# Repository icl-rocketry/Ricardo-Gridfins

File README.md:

# Ricardo-Gridfins
gridfin controller

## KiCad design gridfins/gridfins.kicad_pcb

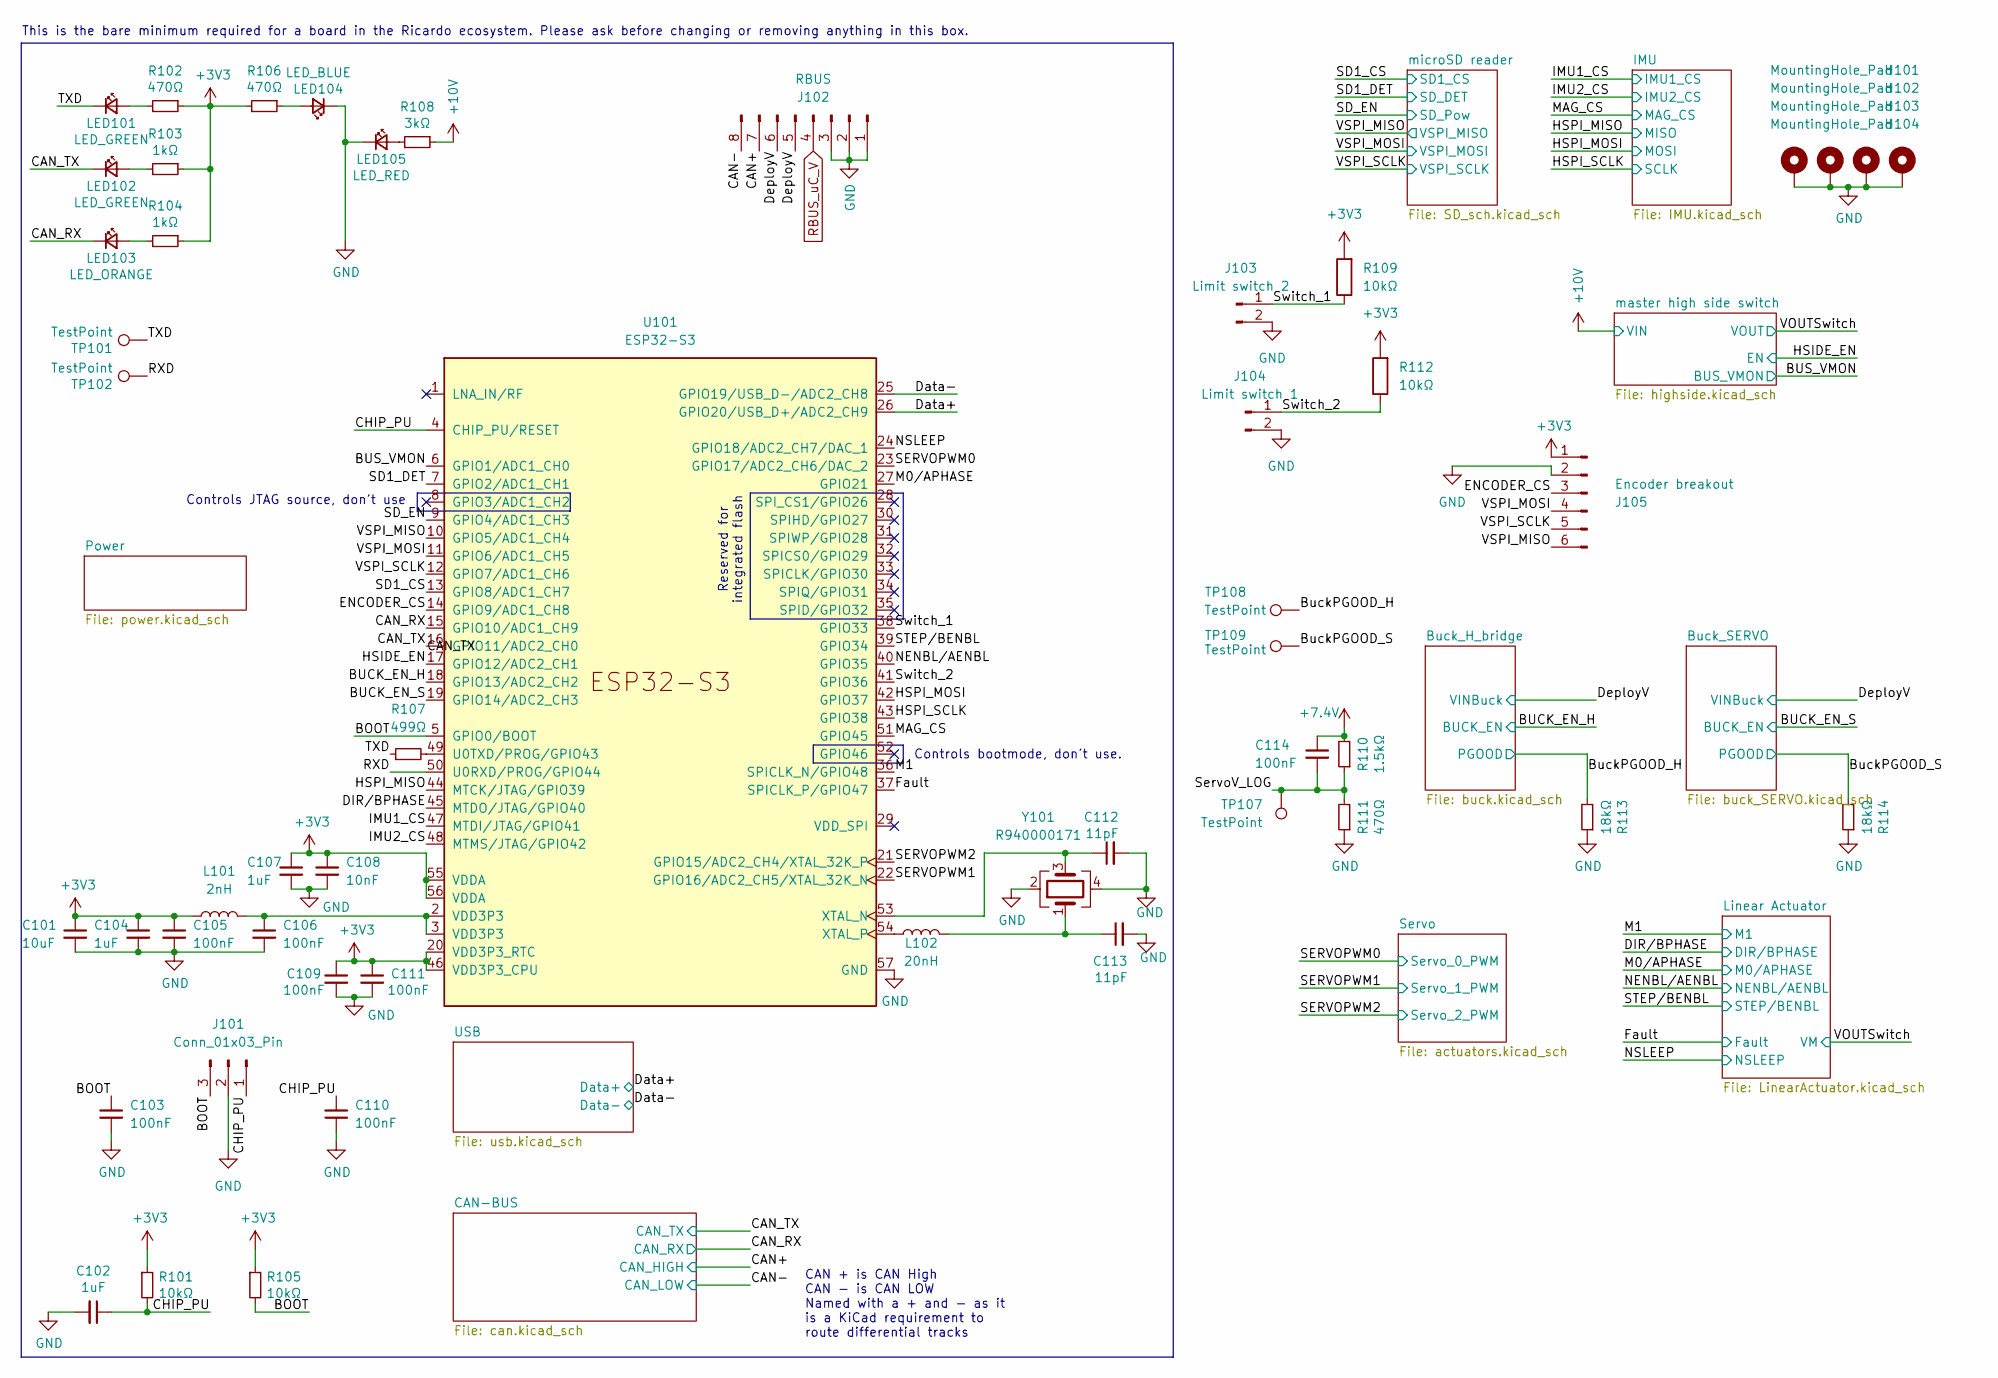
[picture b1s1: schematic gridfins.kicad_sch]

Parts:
C101: 10uF; C_0402_1005Metric
C102, C104, C107: 1uF; C_0402_1005Metric
C103, C105, C106, C109, C110, C111, C114: 100nF; C_0402_1005Metric
C108: 10nF; C_0402_1005Metric
C112, C113: 11pF; C_0402_1005Metric
H101, H102, H103, H104: MountingHole_Pad; MountingHole_3.2mm_M3_DIN965_Pad
J101: Conn_01x03_Pin; PinHeader_1x03_P1.00mm_Vertical
J102: RBUS; Molex_Mini-Fit_Jr_5569-08A2_2x04_P4.20mm_Horizontal
J103: Limit switch 2; PinHeader_1x02_P2.54mm_Vertical
J104: Limit switch 1; PinHeader_1x02_P2.54mm_Vertical
J105: Encoder breakout; PinHeader_2x03_P2.54mm_Vertical
L101: 2nH; L_0402_1005Metric
L102: 20nH; L_0402_1005Metric
LED101, LED102: LED_GREEN; LED_0402_1005Metric
LED103: LED_ORANGE; LED_0402_1005Metric
LED104: LED_BLUE; LED_0402_1005Metric
LED105: LED_RED; LED_0402_1005Metric
R101, R105, R109, R112: 10kΩ; R_0402_1005Metric
R102, R106, R111: 470Ω; R_0402_1005Metric
R103, R104: 1kΩ; R_0402_1005Metric
R107: 499Ω; R_0402_1005Metric
R108: 3kΩ; R_0402_1005Metric
R110: 1.5kΩ; R_0402_1005Metric
R113, R114: 18kΩ; R_0402_1005Metric
TP101, TP102, TP107, TP108, TP109: TestPoint; TestPoint_Pad_D1.0mm
U101: ESP32-S3; QFN40P700X700X90-57N
Y101: R940000171; Crystal_SMD_2016-4Pin_2.0x1.6mm

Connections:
+3V3: C101.1, C104.1, C105.1, C107.1, C108.1, C109.1, C111.1, J105.1, L101.1, R101.1, R102.1, R103.1, R104.1, R105.1, R106.2, R109.2, R112.2, U101.20 (VDD3P3_RTC), U101.46 (VDD3P3_CPU), U101.55 (VDDA), U101.56 (VDDA); also elsewhere on the board
+7.4V: C114.1, R110.2; also elsewhere on the board
+10V: R108.1; also elsewhere on the board
/BOOT: C103.1, J101.3, R105.2, U101.5 (GPIO0/BOOT)
/BUCK_EN_H: U101.18 (GPIO13/ADC2_CH2); also elsewhere on the board
/BUCK_EN_S: U101.19 (GPIO14/ADC2_CH3); also elsewhere on the board
/BUS_VMON: U101.6 (GPIO1/ADC1_CH0); also elsewhere on the board
/BuckPGOOD_H: R113.2, TP108.1 (1_1); also elsewhere on the board
/BuckPGOOD_S: R114.2, TP109.1 (1_1); also elsewhere on the board
/CAN+: J102.7; also elsewhere on the board
/CAN-: J102.8; also elsewhere on the board
/CAN_RX: LED103.1 (K), U101.15 (GPIO10/ADC1_CH9); also elsewhere on the board
/CAN_TX: LED102.1 (K), U101.16 (GPIO11/ADC2_CH0); also elsewhere on the board
/CHIP_PU: C102.1, C110.2, J101.1, R101.2, U101.4 (CHIP_PU/RESET)
/DIR/BPHASE: U101.45 (MTDO/JTAG/GPIO40); also elsewhere on the board
/Data+: U101.26 (GPIO20/USB_D+/ADC2_CH9); also elsewhere on the board
/Data-: U101.25 (GPIO19/USB_D-/ADC2_CH8); also elsewhere on the board
/DeployV: J102.5, J102.6; also elsewhere on the board
/ENCODER_CS: J105.3, U101.14 (GPIO9/ADC1_CH8)
/Fault: U101.37 (SPICLK_P/GPIO47); also elsewhere on the board
/HSIDE_EN: U101.17 (GPIO12/ADC2_CH1); also elsewhere on the board
/HSPI_MISO: U101.44 (MTCK/JTAG/GPIO39); also elsewhere on the board
/HSPI_MOSI: U101.42 (GPIO37); also elsewhere on the board
/HSPI_SCLK: U101.43 (GPIO38); also elsewhere on the board
/IMU1_CS: U101.47 (MTDI/JTAG/GPIO41); also elsewhere on the board
/IMU2_CS: U101.48 (MTMS/JTAG/GPIO42); also elsewhere on the board
/M0/APHASE: U101.27 (GPIO21); also elsewhere on the board
/M1: U101.36 (SPICLK_N/GPIO48); also elsewhere on the board
/MAG_CS: U101.51 (GPIO45); also elsewhere on the board
/NENBL/AENBL: U101.40 (GPIO35); also elsewhere on the board
/NSLEEP: U101.24 (GPIO18/ADC2_CH7/DAC_1); also elsewhere on the board
/RXD: TP102.1 (1_1), U101.50 (U0RXD/PROG/GPIO44)
/SD1_CS: U101.13 (GPIO8/ADC1_CH7); also elsewhere on the board
/SD1_DET: U101.7 (GPIO2/ADC1_CH1); also elsewhere on the board
/SD_EN: U101.9 (GPIO4/ADC1_CH3); also elsewhere on the board
/SERVOPWM0: U101.23 (GPIO17/ADC2_CH6/DAC_2); also elsewhere on the board
/SERVOPWM1: U101.22 (GPIO16/ADC2_CH5/XTAL_32K_N); also elsewhere on the board
/SERVOPWM2: U101.21 (GPIO15/ADC2_CH4/XTAL_32K_P); also elsewhere on the board
/STEP/BENBL: U101.39 (GPIO34); also elsewhere on the board
/ServoV_LOG: C114.2, R110.1, R111.2, TP107.1 (1_1)
/Switch_1: J103.1, R109.1, U101.38 (GPIO33)
/Switch_2: J104.1, R112.1, U101.41 (GPIO36)
/TXD: LED101.1 (K), R107.1, TP101.1 (1_1)
/VSPI_MISO: J105.6, U101.10 (GPIO5/ADC1_CH4); also elsewhere on the board
/VSPI_MOSI: J105.4, U101.11 (GPIO6/ADC1_CH5); also elsewhere on the board
/VSPI_SCLK: J105.5, U101.12 (GPIO7/ADC1_CH6); also elsewhere on the board
GND: C101.2, C102.2, C103.2, C104.2, C105.2, C106.2, C107.2, C108.2, C109.2, C110.1, C111.2, C112.2, C113.2, H101.1 (1_1), H102.1 (1_1), H103.1 (1_1), H104.1 (1_1), J101.2, J102.1, J102.2, J102.3, J103.2, J104.2, J105.2, LED104.1 (K), LED105.1 (K), R111.1, R113.1, R114.1, U101.57 (GND), Y101.2, Y101.4; also elsewhere on the board
unnamed: C106.1, L101.2, U101.2 (VDD3P3), U101.3 (VDD3P3)
unnamed: C113.1, L102.2, Y101.1
unnamed: LED101.2 (A), R102.2
unnamed: LED102.2 (A), R103.2
unnamed: LED103.2 (A), R104.2
unnamed: LED104.2 (A), R106.1
unnamed: LED105.2 (A), R108.2
unnamed: R107.2, U101.49 (U0TXD/PROG/GPIO43)
unnamed: C112.1, U101.53 (XTAL_N), Y101.3
unnamed: L102.1, U101.54 (XTAL_P)
RBUS_uC_V: J102.4; also elsewhere on the board

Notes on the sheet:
Controls bootmode, don't use.
This is the bare minimum required for a board in the Ricardo ecosystem. Please ask before changing or removing anything in this box.
CAN + is CAN High CAN - is CAN LOW Named with a + and - as it is a KiCad requirement to route differential tracks
Controls JTAG source, don't use
Reserved for integrated flash

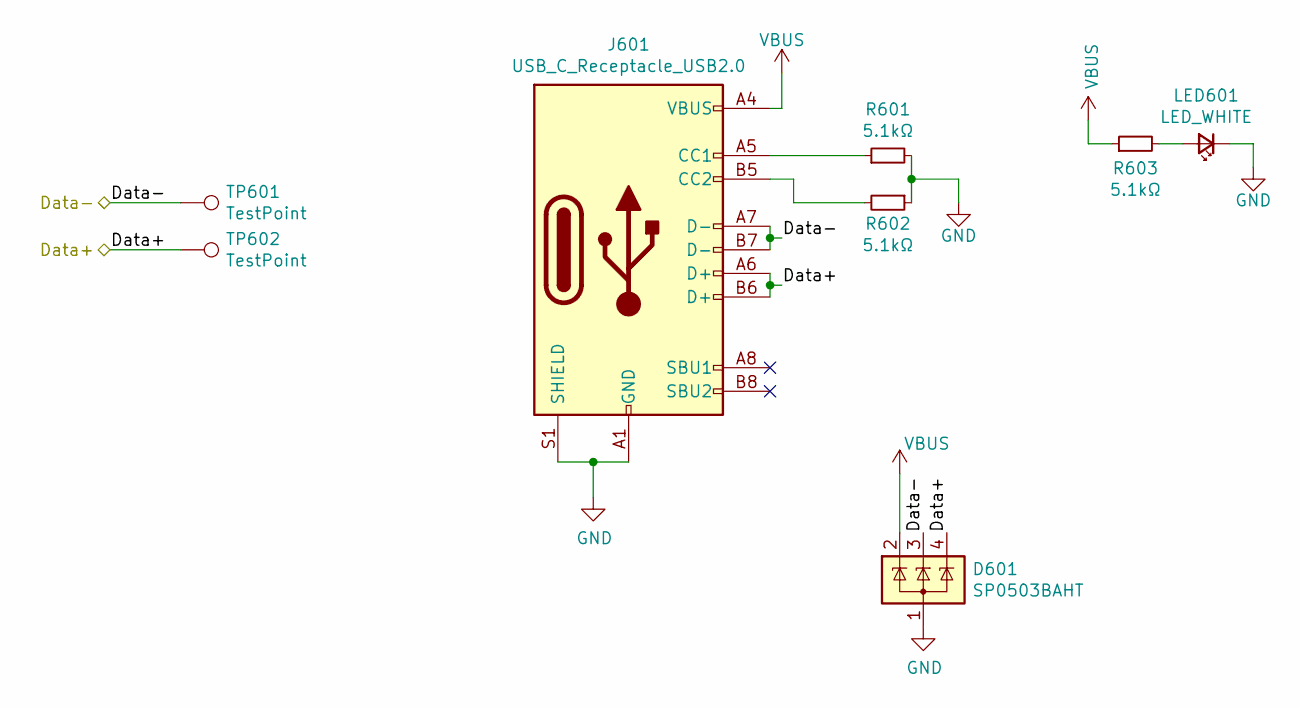
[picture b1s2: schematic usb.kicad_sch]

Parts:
D601: SP0503BAHT; SOT-143
J601: USB_C_Receptacle_USB2.0; USB_C_Receptacle_Palconn_UTC16-G
LED601: LED_WHITE; LED_0402_1005Metric
R601, R602, R603: 5.1kΩ; R_0402_1005Metric
TP601, TP602: TestPoint; TestPoint_Pad_D1.0mm

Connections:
/Data+: D601.4 (K), J601.A6 (D+), J601.B6 (D+), TP602.1 (1_1); also elsewhere on the board
/Data-: D601.3 (K), J601.A7 (D-), J601.B7 (D-), TP601.1 (1_1); also elsewhere on the board
GND: D601.1 (A), J601.A1 (GND), J601.A12 (GND), J601.B1 (GND), J601.B12 (GND), J601.S1 (SHIELD), LED601.1 (K), R601.2, R602.1; also elsewhere on the board
unnamed: J601.A5 (CC1), R601.1
unnamed: J601.B5 (CC2), R602.2
unnamed: LED601.2 (A), R603.2
VBUS: D601.2 (K), J601.A4 (VBUS), J601.A9 (VBUS), J601.B4 (VBUS), J601.B9 (VBUS), R603.1; also elsewhere on the board

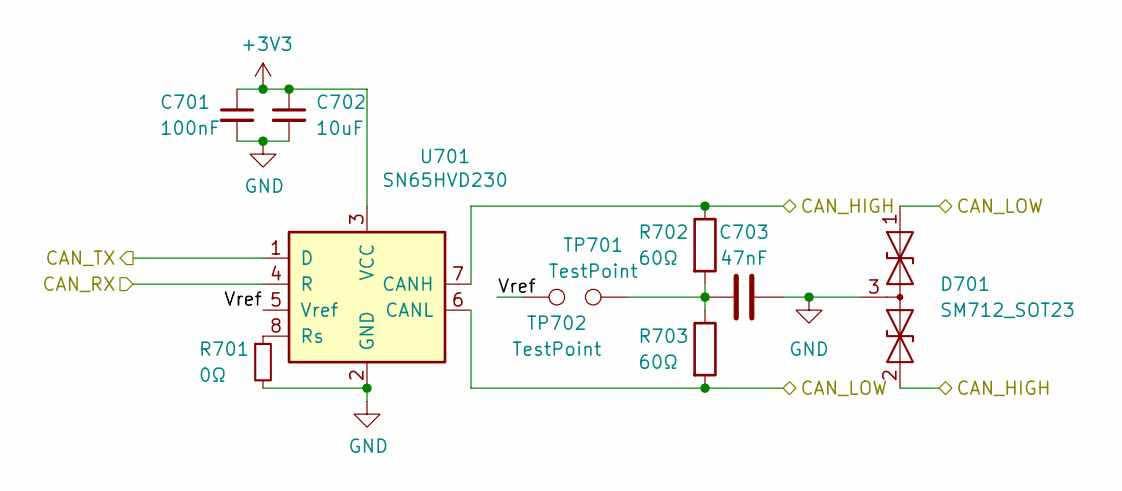
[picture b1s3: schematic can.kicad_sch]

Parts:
C701: 100nF; C_0402_1005Metric
C702: 10uF; C_0402_1005Metric
C703: 47nF; C_0402_1005Metric
D701: SM712_SOT23; SOT-23
R701: 0Ω; R_0603_1608Metric
R702, R703: 60Ω; R_0603_1608Metric
TP701, TP702: TestPoint
U701: SN65HVD230; SOIC-8_3.9x4.9mm_P1.27mm

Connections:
+3V3: C701.1, C702.1, U701.3 (VCC); also elsewhere on the board
/CAN+: D701.2 (A2), R702.1, U701.7 (CANH); also elsewhere on the board
/CAN-: D701.1 (A1), R703.2, U701.6 (CANL); also elsewhere on the board
/CAN-BUS/Vref: TP702.1 (1_1), U701.5 (Vref)
/CAN_RX: U701.4 (R); also elsewhere on the board
/CAN_TX: U701.1 (D); also elsewhere on the board
GND: C701.2, C702.2, C703.2, D701.3 (common), R701.2, U701.2 (GND); also elsewhere on the board
unnamed: C703.1, R702.2, R703.1, TP701.1 (1_1)
unnamed: R701.1, U701.8 (Rs)

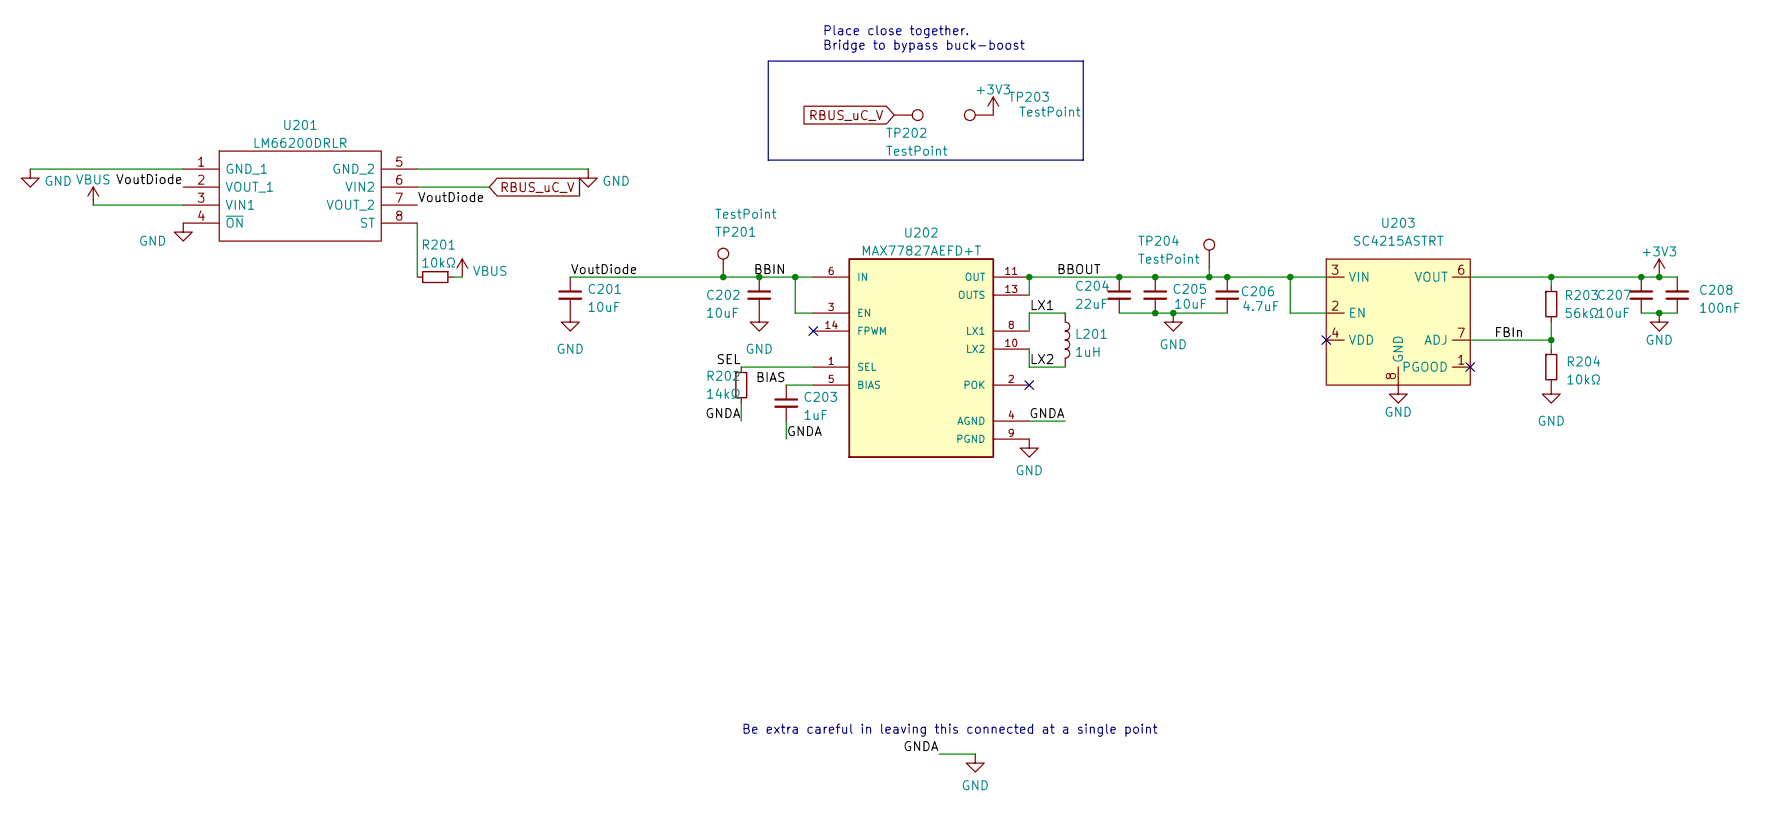
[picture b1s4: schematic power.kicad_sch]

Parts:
C201, C205, C207: 10uF; C_0402_1005Metric
C202: 10uF; C_0603_1608Metric
C203: 1uF; C_0402_1005Metric
C204: 22uF; C_0603_1608Metric
C206: 4.7uF; C_0402_1005Metric
C208: 100nF; C_0402_1005Metric
L201: 1uH; L_0805_2012Metric
R201, R204: 10kΩ; R_0402_1005Metric
R202: 14kΩ; R_0402_1005Metric
R203: 56kΩ; R_0402_1005Metric
TP201, TP202, TP203, TP204: TestPoint; TestPoint_Pad_D1.5mm
U201: LM66200DRLR; SOTFL50P160X60-8N; Manufacturer_Part_Number LM66200DRLR; Mouser Part Number 595-LM66200DRLR
U202: MAX77827AEFD+T; CONV_MAX77827AEFD+T; PARTREV B
U203: SC4215ASTRT; SOIC127P599X175-9N

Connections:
+3V3: C207.2, C208.2, R203.1, TP203.1 (1_1), U203.6 (VOUT); also elsewhere on the board
/Power/BBIN: C201.1, C202.1, TP201.1 (1_1), U201.2 (VOUT_1), U201.7 (VOUT_2), U202.3 (EN), U202.6 (IN)
/Power/BBOUT: C204.1, C205.1, C206.1, TP204.1 (1_1), U202.11 (OUT), U202.13 (OUTS), U203.2 (EN), U203.3 (VIN)
/Power/BIAS: C203.1, U202.5 (BIAS)
/Power/FBIn: R203.2, R204.1, U203.7 (ADJ)
/Power/LX1: L201.1, U202.8 (LX1)
/Power/LX2: L201.2, U202.10 (LX2)
/Power/SEL: R202.1, U202.1 (SEL)
GND: C201.2, C202.2, C203.2, C204.2, C205.2, C206.2, C207.1, C208.1, R202.2, R204.2, U201.1 (GND_1), U201.4 (~ON), U201.5 (GND_2), U202.4 (AGND), U202.9 (PGND), U203.8 (GND), U203.9 (GND); also elsewhere on the board
unnamed: R201.2, U201.8 (ST)
RBUS_uC_V: TP202.1 (1_1), U201.6 (VIN2); also elsewhere on the board
VBUS: R201.1, U201.3 (VIN1); also elsewhere on the board

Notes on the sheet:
Place close together. Bridge to bypass buck-boost
Be extra careful in leaving this connected at a single point

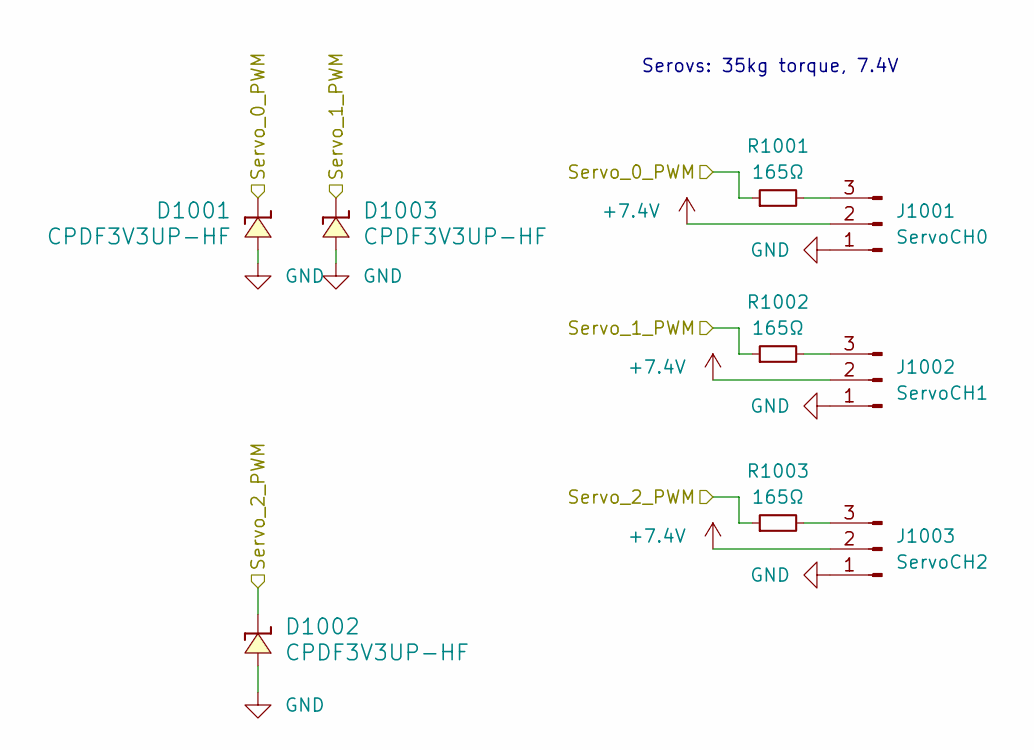
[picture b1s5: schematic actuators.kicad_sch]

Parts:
D1001, D1002, D1003: CPDF3V3UP-HF; CPD
J1001: ServoCH0; Molex_Nano-Fit_105313-xx03_1x03_P2.50mm_Horizontal
J1002: ServoCH1; Molex_Nano-Fit_105313-xx03_1x03_P2.50mm_Horizontal
J1003: ServoCH2; Molex_Nano-Fit_105313-xx03_1x03_P2.50mm_Horizontal
R1001, R1002, R1003: 165Ω; R_0402_1005Metric; MPN RK73H1ETTP1650F

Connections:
+7.4V: J1001.2, J1002.2, J1003.2; also elsewhere on the board
/SERVOPWM0: D1001.2, R1001.1; also elsewhere on the board
/SERVOPWM1: D1003.2, R1002.1; also elsewhere on the board
/SERVOPWM2: D1002.2, R1003.1; also elsewhere on the board
GND: D1001.1, D1002.1, D1003.1, J1001.1, J1002.1, J1003.1; also elsewhere on the board
unnamed: J1001.3, R1001.2
unnamed: J1002.3, R1002.2
unnamed: J1003.3, R1003.2

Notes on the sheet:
Serovs: 35kg torque, 7.4V

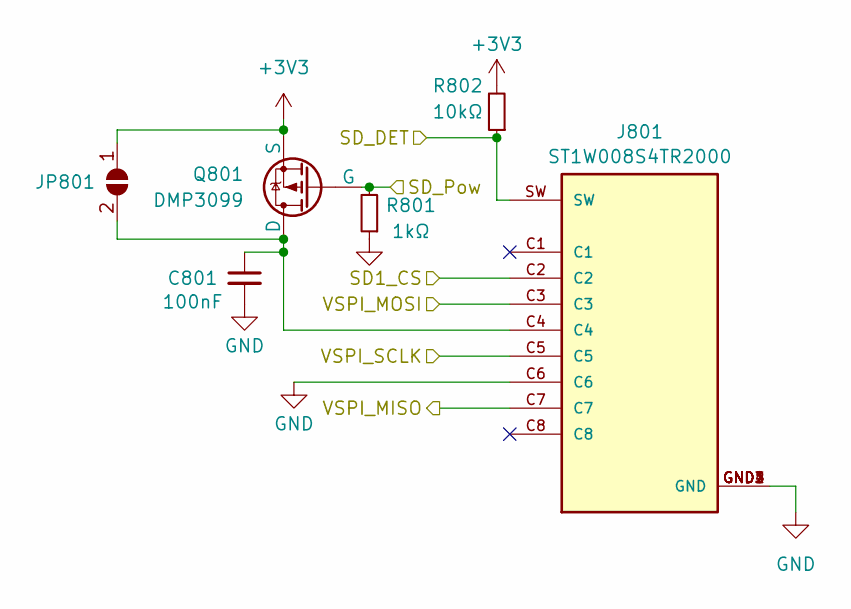
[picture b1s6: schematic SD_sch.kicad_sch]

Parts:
C801: 100nF; C_0402_1005Metric
J801: ST1W008S4TR2000; JAE_ST1W008S4TR2000; PARTREV 1
JP801: SolderJumper_2_Open; SmallerSolderJP
Q801: DMP3099; SOT-23; MPN DMP3099L
R801: 1kΩ; R_0402_1005Metric
R802: 10kΩ; R_0402_1005Metric

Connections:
+3V3: JP801.1 (A), Q801.3 (S), R802.2; also elsewhere on the board
/SD1_CS: J801.C2; also elsewhere on the board
/SD1_DET: J801.SW, R802.1; also elsewhere on the board
/SD_EN: Q801.2 (G), R801.2; also elsewhere on the board
/VSPI_MISO: J801.C7; also elsewhere on the board
/VSPI_MOSI: J801.C3; also elsewhere on the board
/VSPI_SCLK: J801.C5; also elsewhere on the board
GND: C801.2, J801.C6, J801.GND1 (GND), J801.GND2 (GND), J801.GND3 (GND), J801.GND4 (GND), R801.1; also elsewhere on the board
unnamed: C801.1, J801.C4, JP801.2 (B), Q801.1 (D)

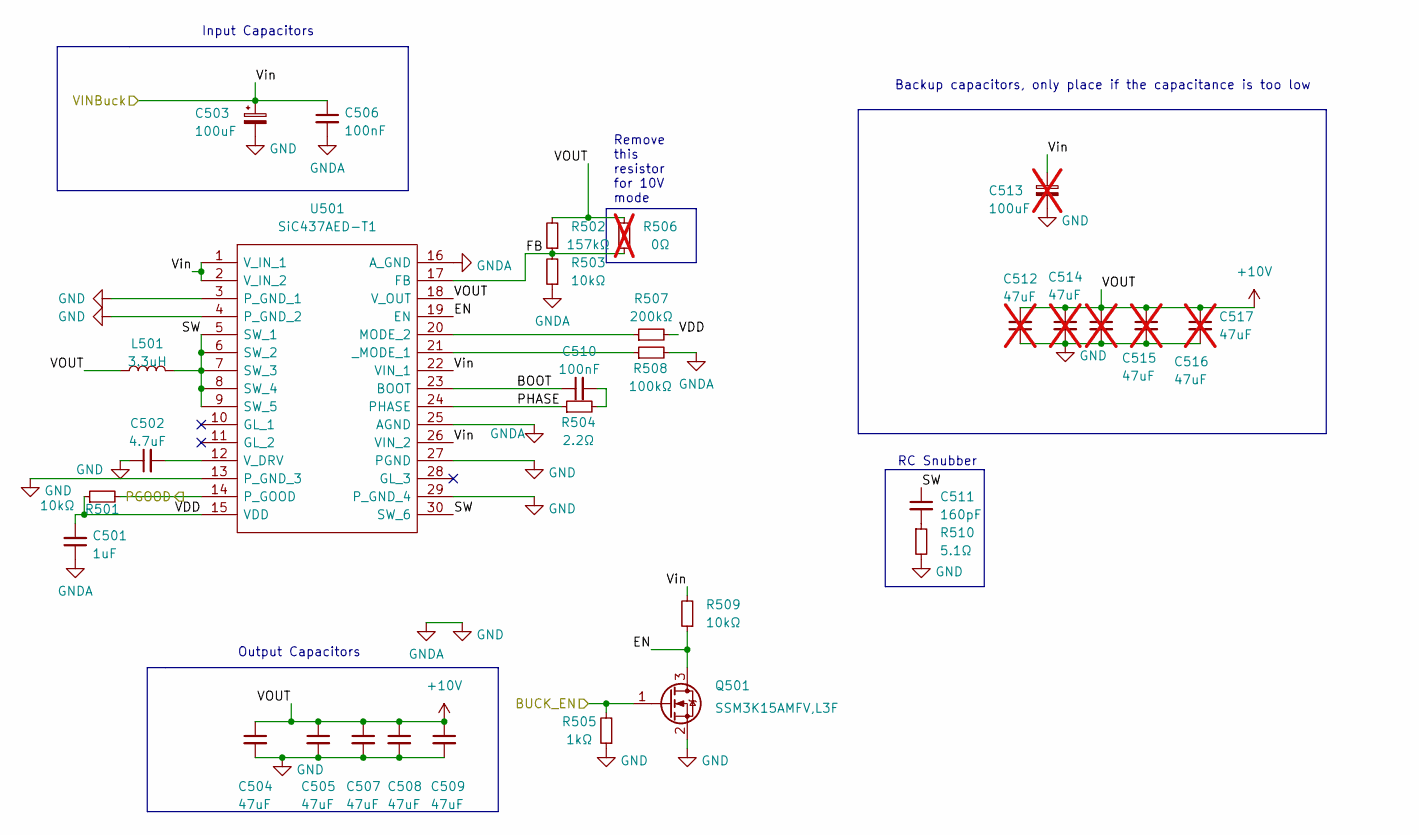
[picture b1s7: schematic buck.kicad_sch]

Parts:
C501: 1uF; C_0402_1005Metric
C502: 4.7uF; C_0402_1005Metric
C503: 100uF; CP_EIA-7360-38_Kemet-E; MPN T52M1107M035C0100
C504, C505, C507, C508, C509: 47uF; C_1206_3216Metric
C506, C510: 100nF; C_0402_1005Metric
C511: 160pF; C_0603_1608Metric
C512, C514, C515, C516, C517: 47uF; C_1206_3216Metric; not fitted
C513: 100uF; CP_EIA-7360-38_Kemet-E; MPN T52M1107M035C0100; not fitted
L501: 3.3uH; WE-XHMI_7070; MPN SPM10065VT-3R3M-D
Q501: SSM3K15AMFV,L3F; SOT-723
R501, R503, R509: 10kΩ; R_0402_1005Metric
R502: 157kΩ; R_0402_1005Metric; MPN ERJ-2RKF1133X
R504: 2.2Ω; R_0402_1005Metric
R505: 1kΩ; R_0402_1005Metric
R506: 0Ω; R_0402_1005Metric; MPN ERJ-2RKF4423X; not fitted
R507: 200kΩ; R_0402_1005Metric
R508: 100kΩ; R_0402_1005Metric
R510: 5.1Ω; R_0603_1608Metric
U501: SiC437AED-T1; SiC437BEDT1GE3; Manufacturer_Part_Number SiC437BED-T1-GE3; Mouser Part Number 78-SIC437BED-T1-GE3

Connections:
+10V: C504.1, C505.1, C507.1, C508.1, C509.1, C512.2, C514.1, C515.1, C516.1, C517.1, L501.2, R502.2, R506.2, U501.18 (V_OUT); also elsewhere on the board
/BUCK_EN_H: Q501.1 (G), R505.2; also elsewhere on the board
/BuckPGOOD_H: R501.2, U501.14 (P_GOOD); also elsewhere on the board
/Buck_H_bridge/BOOT: C510.1, U501.23 (BOOT)
/Buck_H_bridge/EN: Q501.3 (D), R509.1, U501.19 (EN)
/Buck_H_bridge/FB: R502.1, R503.2, R506.1, U501.17 (FB)
/Buck_H_bridge/PHASE: R504.1, U501.24 (PHASE)
/Buck_H_bridge/SW: C511.1, L501.1, U501.5 (SW_1), U501.6 (SW_2), U501.7 (SW_3), U501.8 (SW_4), U501.9 (SW_5), U501.30 (SW_6)
/Buck_H_bridge/VDD: C501.2, R501.1, R507.2, U501.15 (VDD)
/DeployV: C503.1, C506.1, C513.1, R509.2, U501.1 (V_IN_1), U501.2 (V_IN_2), U501.22 (VIN_1), U501.26 (VIN_2); also elsewhere on the board
GND: C501.1, C502.1, C503.2, C504.2, C505.2, C506.2, C507.2, C508.2, C509.2, C512.1, C513.2, C514.2, C515.2, C516.2, C517.2, Q501.2 (S), R503.1, R505.1, R508.2, R510.2, U501.3 (P_GND_1), U501.4 (P_GND_2), U501.13 (P_GND_3), U501.16 (A_GND), U501.25 (AGND), U501.27 (PGND), U501.29 (P_GND_4); also elsewhere on the board
unnamed: C510.2, R504.2
unnamed: C511.2, R510.1
unnamed: R507.1, U501.20 (MODE_2)
unnamed: C502.2, U501.12 (V_DRV)
unnamed: R508.1, U501.21 (_MODE_1)

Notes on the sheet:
Output Capacitors
RC Snubber
Input Capacitors
Backup capacitors, only place if the capacitance is too low
Remove this resistor for 10V mode

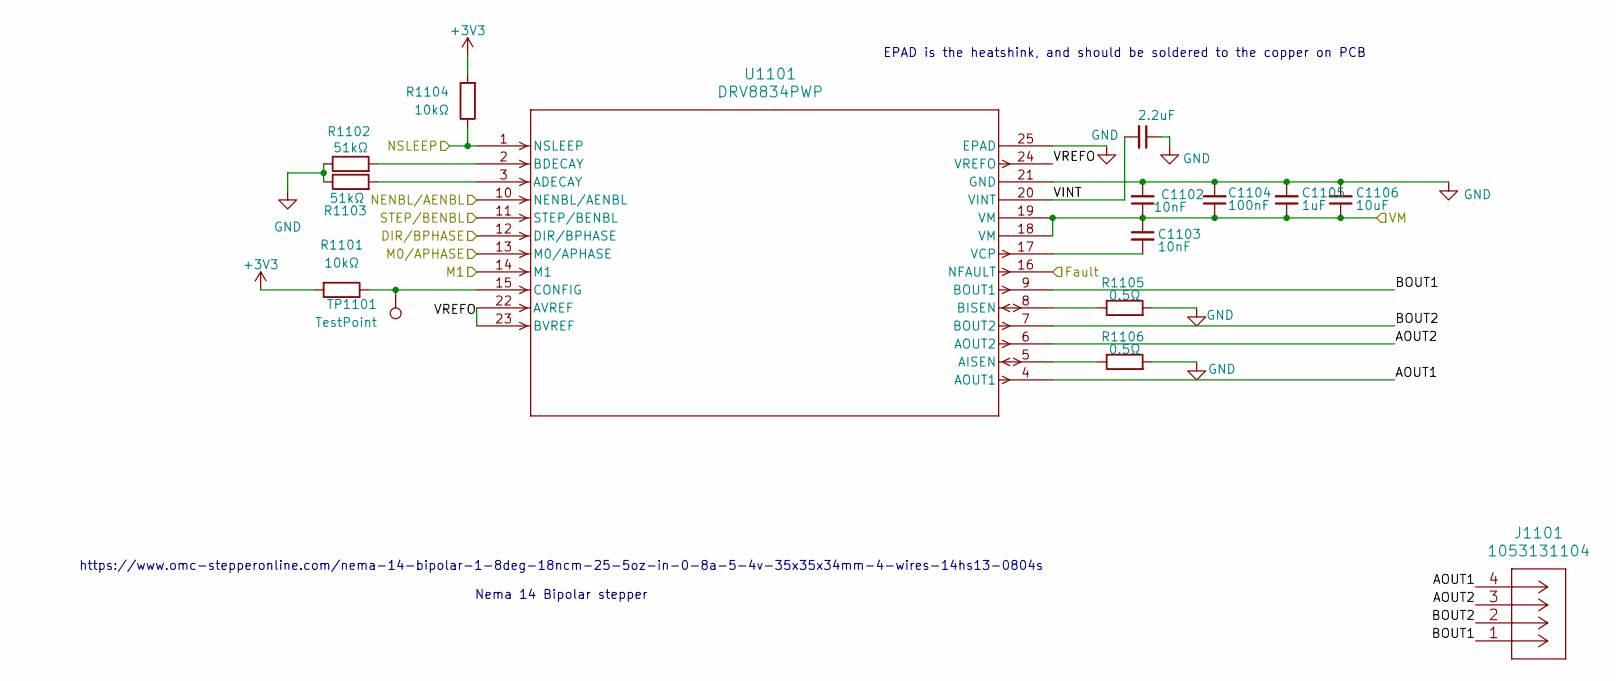
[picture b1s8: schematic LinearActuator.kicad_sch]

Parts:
C1101: 2.2uF; C_0402_1005Metric
C1102, C1103: 10nF; C_0402_1005Metric
C1104: 100nF; C_0402_1005Metric
C1105: 1uF; C_0402_1005Metric
C1106: 10uF; C_0805_2012Metric
J1101: 1053131104; Molex_Nano-Fit_105313-xx04_1x04_P2.50mm_Horizontal
R1101, R1104: 10kΩ; R_0402_1005Metric
R1102, R1103: 51kΩ; R_0402_1005Metric
R1105, R1106: 0.5Ω; R_2512_6332Metric
TP1101: TestPoint; TestPoint_Pad_D1.0mm
U1101: DRV8834PWP; PWP_24

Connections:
+3V3: R1101.2, R1104.2; also elsewhere on the board
/DIR/BPHASE: U1101.12 (DIR/BPHASE); also elsewhere on the board
/Fault: U1101.16 (NFAULT); also elsewhere on the board
/Linear Actuator/AOUT1: J1101.4, U1101.4 (AOUT1)
/Linear Actuator/AOUT2: J1101.3, U1101.6 (AOUT2)
/Linear Actuator/BOUT1: J1101.1, U1101.9 (BOUT1)
/Linear Actuator/BOUT2: J1101.2, U1101.7 (BOUT2)
/Linear Actuator/VINT: C1101.2, U1101.20 (VINT)
/Linear Actuator/VREFO: U1101.22 (AVREF), U1101.23 (BVREF), U1101.24 (VREFO)
/M0/APHASE: U1101.13 (M0/APHASE); also elsewhere on the board
/M1: U1101.14 (M1); also elsewhere on the board
/NENBL/AENBL: U1101.10 (NENBL/AENBL); also elsewhere on the board
/NSLEEP: R1104.1, U1101.1 (NSLEEP); also elsewhere on the board
/STEP/BENBL: U1101.11 (STEP/BENBL); also elsewhere on the board
/VOUTSwitch: C1102.1, C1103.1, C1104.1, C1105.1, C1106.1, U1101.18 (VM), U1101.19 (VM); also elsewhere on the board
GND: C1101.1, C1102.2, C1104.2, C1105.2, C1106.2, R1102.1, R1103.1, R1105.2, R1106.2, U1101.21 (GND), U1101.25 (EPAD); also elsewhere on the board
unnamed: R1103.2, U1101.3 (ADECAY)
unnamed: R1106.1, U1101.5 (AISEN)
unnamed: R1102.2, U1101.2 (BDECAY)
unnamed: R1105.1, U1101.8 (BISEN)
unnamed: R1101.1, TP1101.1 (1_1), U1101.15 (CONFIG)
unnamed: C1103.2, U1101.17 (VCP)

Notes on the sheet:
https://www.omc-stepperonline.com/nema-14-bipolar-1-8deg-18ncm-25-5oz-in-0-8a-5-4v-35x35x34mm-4-wires-14hs13-0804s Nema 14 Bipolar stepper
EPAD is the heatshink, and should be soldered to the copper on PCB

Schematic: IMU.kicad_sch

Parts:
C901, C904, C906: 10uF; C_0402_1005Metric
C902, C903, C905: 100nF; C_0402_1005Metric
C907: 1uF; C_0402_1005Metric
U901: H3LIS331DLTR; QFN300X300X100-16N; PARTREV 2
U902: 2536030320001; Mouser Part Number 710-2536030320001
U903: MMC5983MA; PQFN50P300X300X100-16N; PARTREV A

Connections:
+3V3: C901.1, C902.1, C903.1, C904.1, C905.1, C907.1, U901.1 (VDD_IO), U901.14 (VDD), U901.15 (VDD), U902.2 (RSVD_1), U902.3 (RSVD_2), U902.5 (VDD_IO), U902.8 (VDD), U902.11 (RSVD_4), U903.2 (VDD), U903.13 (VDDIO); also elsewhere on the board
/HSPI_MISO: U901.7 (SDO/SA0), U902.1 (SAO), U903.5 (SPI_SDO); also elsewhere on the board
/HSPI_MOSI: U901.6 (SDA/SDI/SDO), U902.14 (SDA), U903.16 (SDA/SPI_SDI); also elsewhere on the board
/HSPI_SCLK: U901.4 (SCL/SPC), U902.13 (SCL), U903.1 (SCL/SPI_SCK); also elsewhere on the board
/IMU1_CS: U902.12 (CS); also elsewhere on the board
/IMU2_CS: U901.8 (CS); also elsewhere on the board
/MAG_CS: U903.4 (~SPI_CS); also elsewhere on the board
GND: C901.2, C902.2, C903.2, C904.2, C905.2, C906.2, C907.2, U901.5 (GND), U901.10 (GND), U901.12 (GND), U901.13 (GND), U901.16 (GND), U902.6 (GND_1), U902.7 (GND_2), U903.9 (GND), U903.11 (GND); also elsewhere on the board
unnamed: C906.1, U903.10 (CAP)

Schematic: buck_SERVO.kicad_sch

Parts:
C401: 1uF; C_0402_1005Metric
C402: 4.7uF; C_0402_1005Metric
C403: 100uF; CP_EIA-7360-38_Kemet-E; MPN T52M1107M035C0100
C404, C405, C407, C408, C409: 47uF; C_1206_3216Metric
C406, C410: 100nF; C_0402_1005Metric
C411: 160pF; C_0603_1608Metric
C412, C414, C415, C416, C417: 47uF; C_1206_3216Metric; not fitted
C413: 100uF; CP_EIA-7360-38_Kemet-E; MPN T52M1107M035C0100; not fitted
L401: 3.3uH; WE-XHMI_7070; MPN SPM10065VT-3R3M-D
Q401: SSM3K15AMFV,L3F; SOT-723
R401, R403, R409: 10kΩ; R_0402_1005Metric
R402: 113kΩ; R_0402_1005Metric; MPN ERJ-2RKF1133X
R404: 2.2Ω; R_0402_1005Metric
R405: 1kΩ; R_0402_1005Metric
R406: 442kΩ; R_0402_1005Metric; MPN ERJ-2RKF4423X
R407: 200kΩ; R_0402_1005Metric
R408: 100kΩ; R_0402_1005Metric
R410: 5.1Ω; R_0603_1608Metric
U401: SiC437AED-T1; SiC437BEDT1GE3; Manufacturer_Part_Number SiC437BED-T1-GE3; Mouser Part Number 78-SIC437BED-T1-GE3

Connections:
+7.4V: C404.1, C405.1, C407.1, C408.1, C409.1, C412.2, C414.1, C415.1, C416.1, C417.1, L401.2, R402.2, R406.2, U401.18 (V_OUT); also elsewhere on the board
/BUCK_EN_S: Q401.1 (G), R405.2; also elsewhere on the board
/BuckPGOOD_S: R401.2, U401.14 (P_GOOD); also elsewhere on the board
/Buck_SERVO/BOOT: C410.1, U401.23 (BOOT)
/Buck_SERVO/EN: Q401.3 (D), R409.1, U401.19 (EN)
/Buck_SERVO/FB: R402.1, R403.2, R406.1, U401.17 (FB)
/Buck_SERVO/PHASE: R404.1, U401.24 (PHASE)
/Buck_SERVO/SW: C411.1, L401.1, U401.5 (SW_1), U401.6 (SW_2), U401.7 (SW_3), U401.8 (SW_4), U401.9 (SW_5), U401.30 (SW_6)
/Buck_SERVO/VDD: C401.2, R401.1, R407.2, U401.15 (VDD)
/DeployV: C403.1, C406.1, C413.1, R409.2, U401.1 (V_IN_1), U401.2 (V_IN_2), U401.22 (VIN_1), U401.26 (VIN_2); also elsewhere on the board
GND: C401.1, C402.1, C403.2, C404.2, C405.2, C406.2, C407.2, C408.2, C409.2, C412.1, C413.2, C414.2, C415.2, C416.2, C417.2, Q401.2 (S), R403.1, R405.1, R408.2, R410.2, U401.3 (P_GND_1), U401.4 (P_GND_2), U401.13 (P_GND_3), U401.16 (A_GND), U401.25 (AGND), U401.27 (PGND), U401.29 (P_GND_4); also elsewhere on the board
unnamed: C410.2, R404.2
unnamed: C411.2, R410.1
unnamed: R407.1, U401.20 (MODE_2)
unnamed: C402.2, U401.12 (V_DRV)
unnamed: R408.1, U401.21 (_MODE_1)

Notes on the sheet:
Input Capacitors
RC Snubber
Output Capacitors
Backup capacitors, only place if the capacitance is too low
Remove this resistor for 7.4V mode

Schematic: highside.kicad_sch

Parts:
C301, C304: 100nF; C_0402_1005Metric
C302: 1uF; C_0402_1005Metric; Voltage Rating DC 50V; MPN GRT188R61H225KE13D
C303: 100nF; C_0603_1608Metric
Q301, Q302: BSZ025N04LS; Manufacturer_Part_Number BSZ025N04LS; Mouser Part Number 726-BSZ025N04LS
R301: 10kΩ; R_0402_1005Metric
R302: 100kΩ; R_0402_1005Metric
R303: 5.1kΩ; R_0402_1005Metric
R304: 4.22kΩ; R_0402_1005Metric
U301: LM74810; SON50P300X300X80-13N-D; Manufacturer_Part_Number LM74810QDRRRQ1; Mouser Part Number 595-LM74810QDRRRQ1

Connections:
+10V: C301.1, Q301.1 (S), Q301.2 (S), Q301.3 (S), Q301.A1 (S), U301.2 (A), U301.3 (VSNS); also elsewhere on the board
/BUS_VMON: R302.2, R303.2; also elsewhere on the board
/HSIDE_EN: R301.1, U301.6 (EN/UVLO); also elsewhere on the board
/VOUTSwitch: C304.1, Q302.1 (S), Q302.2 (S), Q302.3 (S), Q302.A1 (S), U301.9 (OUT); also elsewhere on the board
/master high side switch/C: C302.1, C303.1, Q301.5 (D), Q301.6 (D), Q301.7 (D), Q301.8 (D), Q301.A5 (D), Q302.5 (D), Q302.6 (D), Q302.7 (D), Q302.8 (D), Q302.A5 (D), U301.10 (VS), U301.12 (C)
/master high side switch/CAP: C302.2, U301.11 (CAP)
/master high side switch/DGate: Q301.4 (G), U301.1 (DGATE)
/master high side switch/HGate: Q302.4 (G), U301.8 (HGATE)
GND: C301.2, C303.2, C304.2, R301.2, R304.1, U301.7 (GND); also elsewhere on the board
unnamed: R303.1, R304.2, U301.5 (OV)
unnamed: R302.1, U301.4 (SW)

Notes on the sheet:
Batt Mon - 3.0V out @ 35V in Overvoltage cutoff - 32V Check sizing script
